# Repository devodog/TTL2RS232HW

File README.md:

# TTL2RS232HW
Circuit schematics and PCB layout

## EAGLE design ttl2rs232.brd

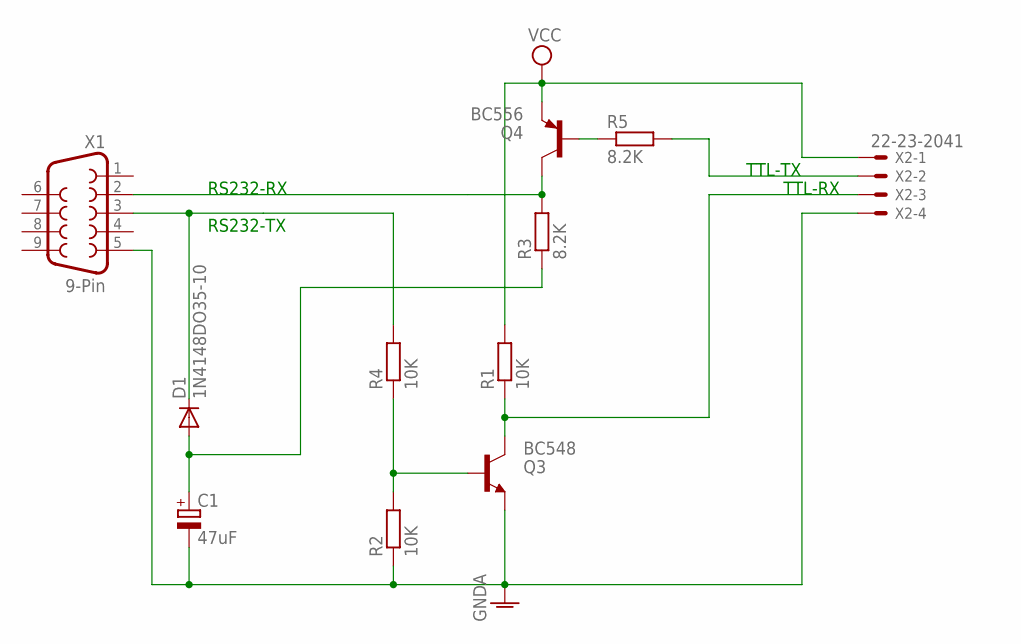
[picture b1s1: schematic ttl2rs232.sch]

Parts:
C1: 47uF; E2,5-7
D1: 1N4148DO35-10; DO35-10
Q3: BC548; TO92-EBC
Q4: BC556; TO92-EBC
R1, R2, R4: 10K; 0207/10
R3, R5: 8.2K; 0207/10
X1: 9-Pin; F09H
X2: 22-23-2041

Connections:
GNDA: C1.-, Q3.E, R2.1, X1.5, X2.4
unnamed: Q3.C, R1.1, X2.3
unnamed: Q3.B, R2.2, R4.1
unnamed: C1.+, D1.A, R3.1
unnamed: D1.C, R4.2, X1.3
unnamed: Q4.C, R3.2, X1.2
unnamed: Q4.B, R5.1
unnamed: R5.2, X2.2
VCC: Q4.E, R1.2, X2.1

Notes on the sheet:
TTL-TX
TTL-RX
RS232-RX
RS232-TX

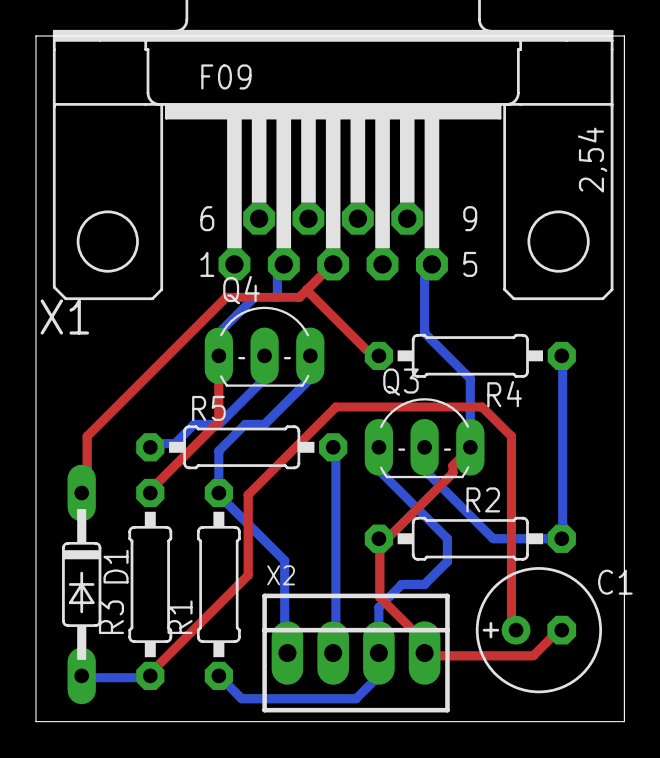
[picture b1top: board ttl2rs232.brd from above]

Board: 2 copper layers, 32.7 x 38.1 mm, 11 parts (0 on the bottom side), 9 nets.

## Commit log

2021-06-30 Version 1.0
2021-07-02 updated PBC wih wider traces
2022-04-13 Adjusted some pcb-text for an assembly pdf drawing
